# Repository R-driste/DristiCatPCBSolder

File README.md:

# DristiCatPCBSolder
Hello! Here is my PCB keychain for HC solder :D. It controls the LEDs using the potentiometer (as a variable resistor) and in response to the brightness level (with the photoresistor). This was my first time fully designing a PCB :D I'm looking forward to soldering it and using it on my bag.
Parts: (1) photoresistor, (1) potentiometer, (1) npn transistor, (6) LEDs, (6) 220ohm resistors and a battery cell.

Cat Image Attribution: <a href="https://www.vecteezy.com/free-vector/cat">Cat Vectors by Vecteezy, Posted by 
Arif Wahyu</a>

# PCB 3D VIEW

# PCB FOOTPRINTS AND SCHEMATIC

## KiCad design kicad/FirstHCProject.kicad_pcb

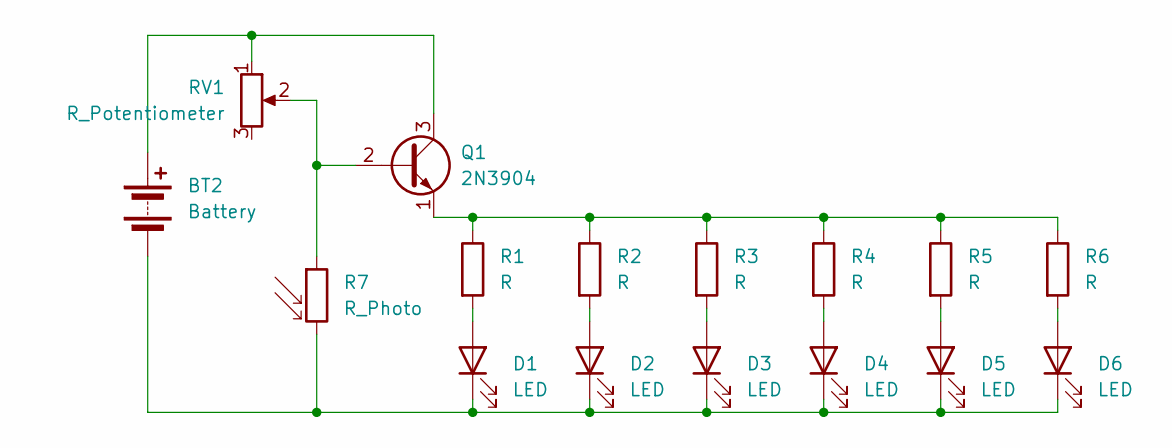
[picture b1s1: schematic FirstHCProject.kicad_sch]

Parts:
BT2: Battery; BatteryHolder_Keystone_3034_1x20mm
D1, D2, D3, D4, D5, D6: LED; LED_D5.0mm
Q1: 2N3904; TO-92_Inline
R1, R2, R3, R4, R5, R6: R; R_Axial_DIN0207_L6.3mm_D2.5mm_P7.62mm_Horizontal
R7: R_Photo; R_LDR_5.1x4.3mm_P3.4mm_Vertical
RV1: R_Potentiometer; Potentiometer_Bourns_3296W_Vertical

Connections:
unnamed: BT2.1 (+), Q1.3 (C), RV1.1
unnamed: BT2.2 (-), D1.1 (K), D2.1 (K), D3.1 (K), D4.1 (K), D5.1 (K), D6.1 (K), R7.2
unnamed: D1.2 (A), R1.2
unnamed: D2.2 (A), R2.2
unnamed: D3.2 (A), R3.2
unnamed: D4.2 (A), R4.2
unnamed: D5.2 (A), R5.2
unnamed: D6.2 (A), R6.2
unnamed: Q1.2 (B), R7.1, RV1.2
unnamed: Q1.1 (E), R1.1, R2.1, R3.1, R4.1, R5.1, R6.1

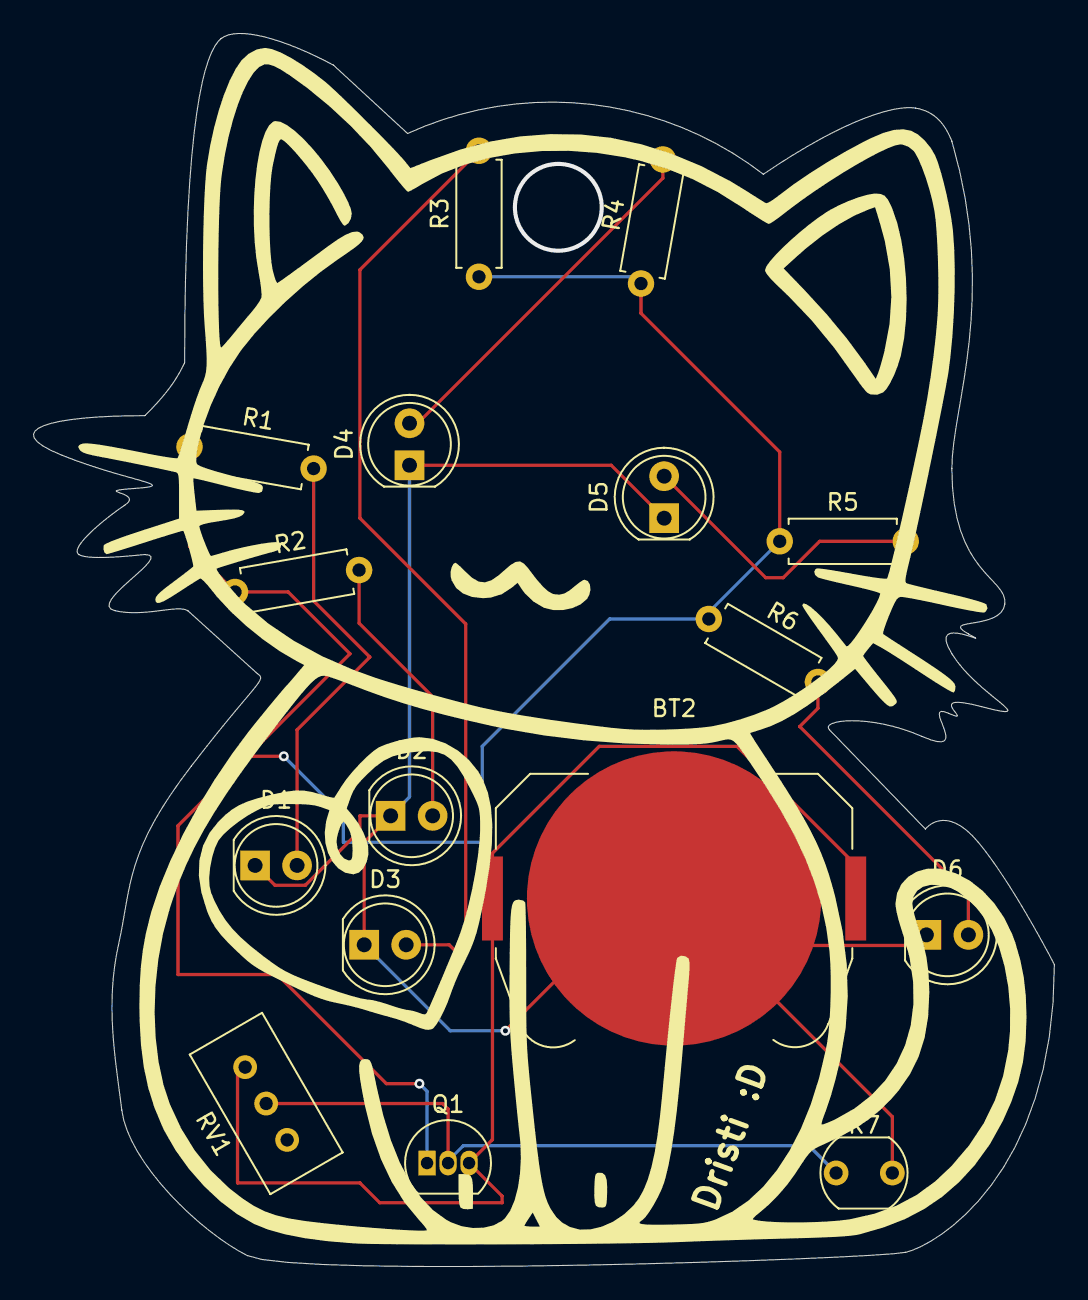
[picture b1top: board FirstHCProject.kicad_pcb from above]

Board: 2 copper layers, 61.7 x 74.6 mm, 17 parts (0 on the bottom side), 10 nets.

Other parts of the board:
Dristi :D: LOGO

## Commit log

2025-07-04 resubmit
2025-07-04 back png
